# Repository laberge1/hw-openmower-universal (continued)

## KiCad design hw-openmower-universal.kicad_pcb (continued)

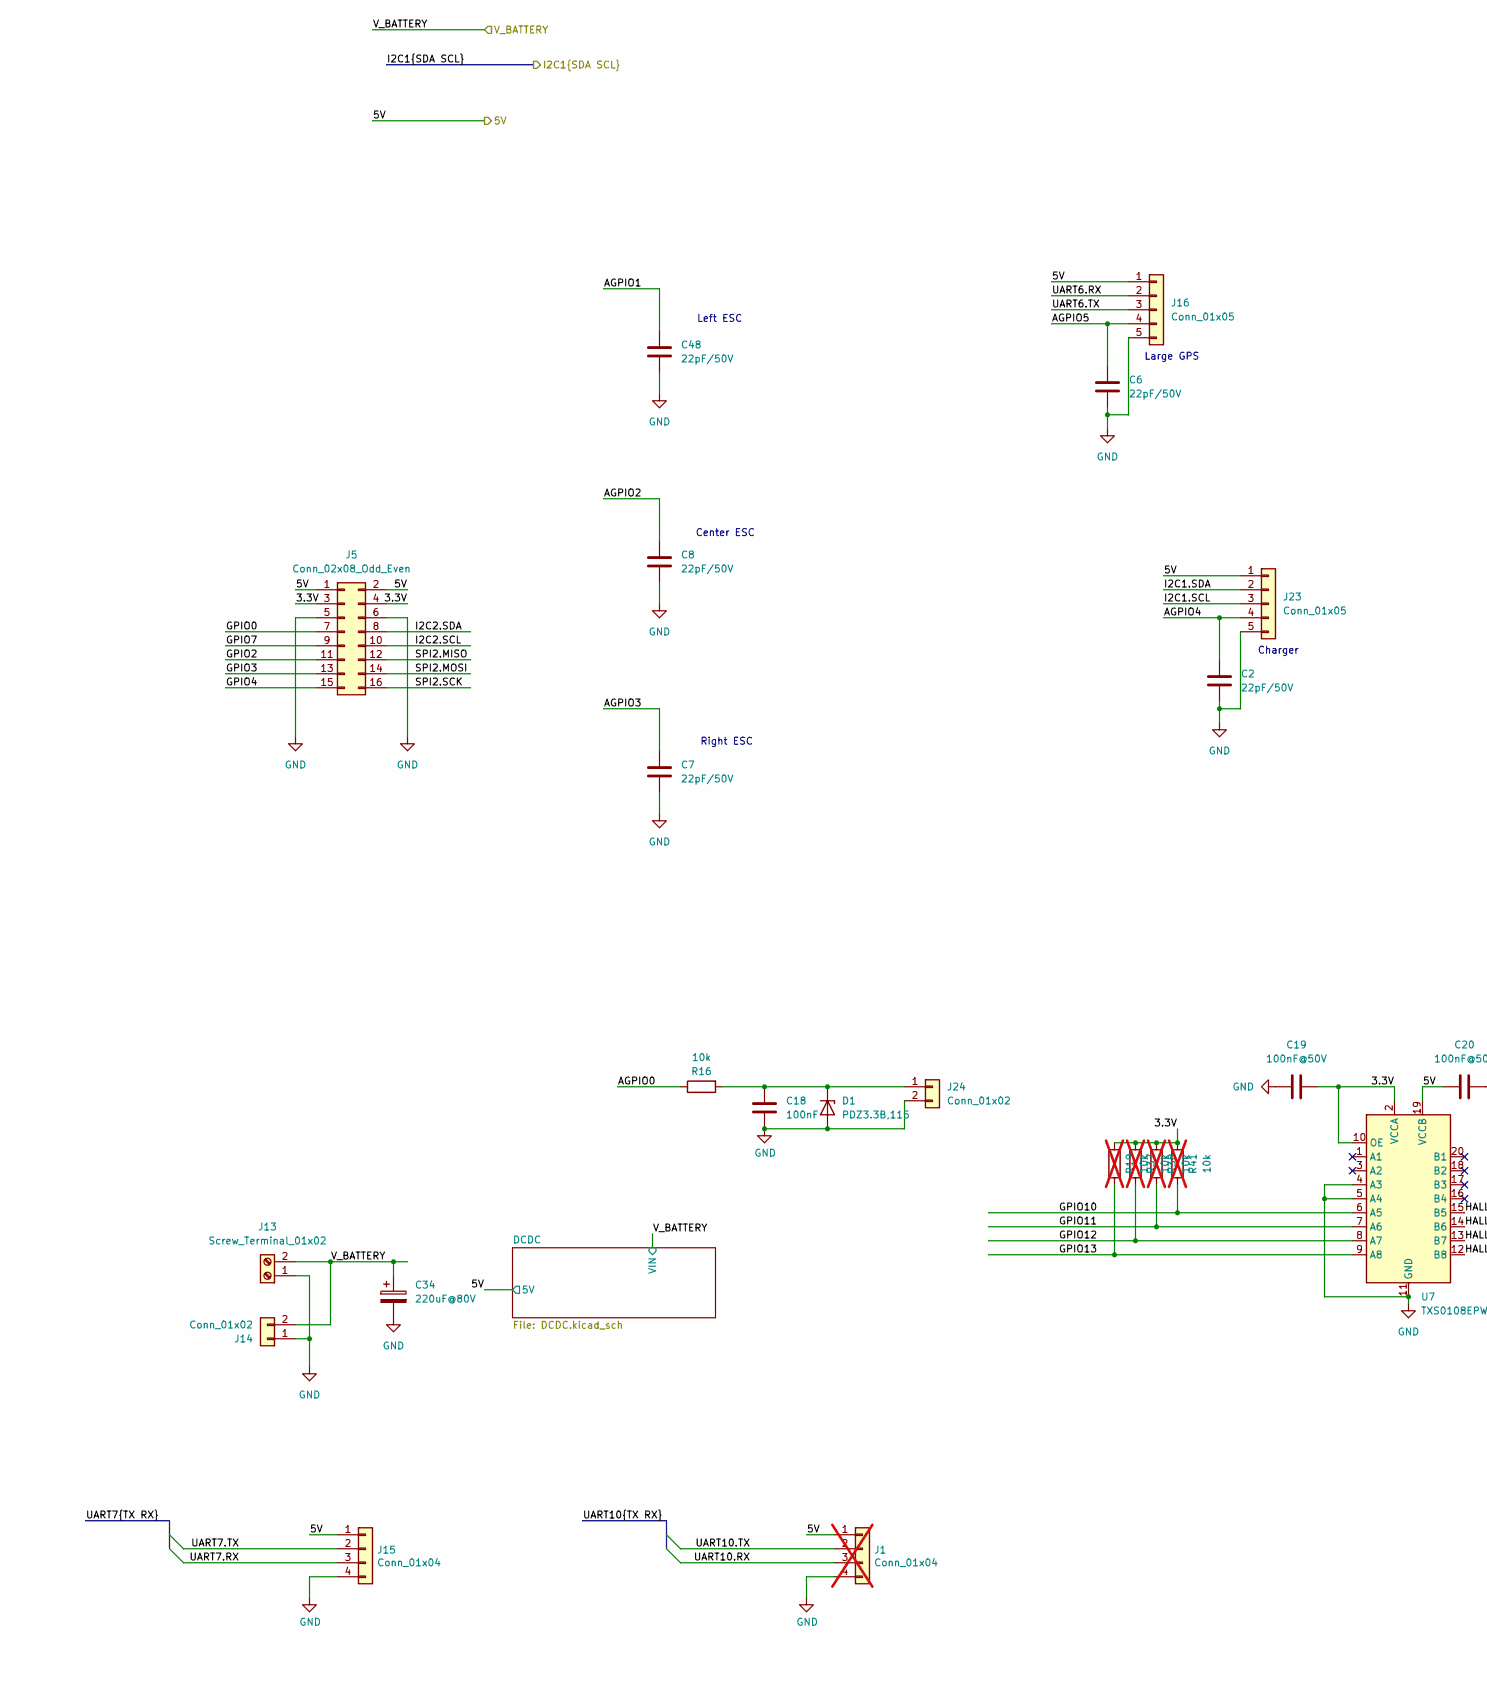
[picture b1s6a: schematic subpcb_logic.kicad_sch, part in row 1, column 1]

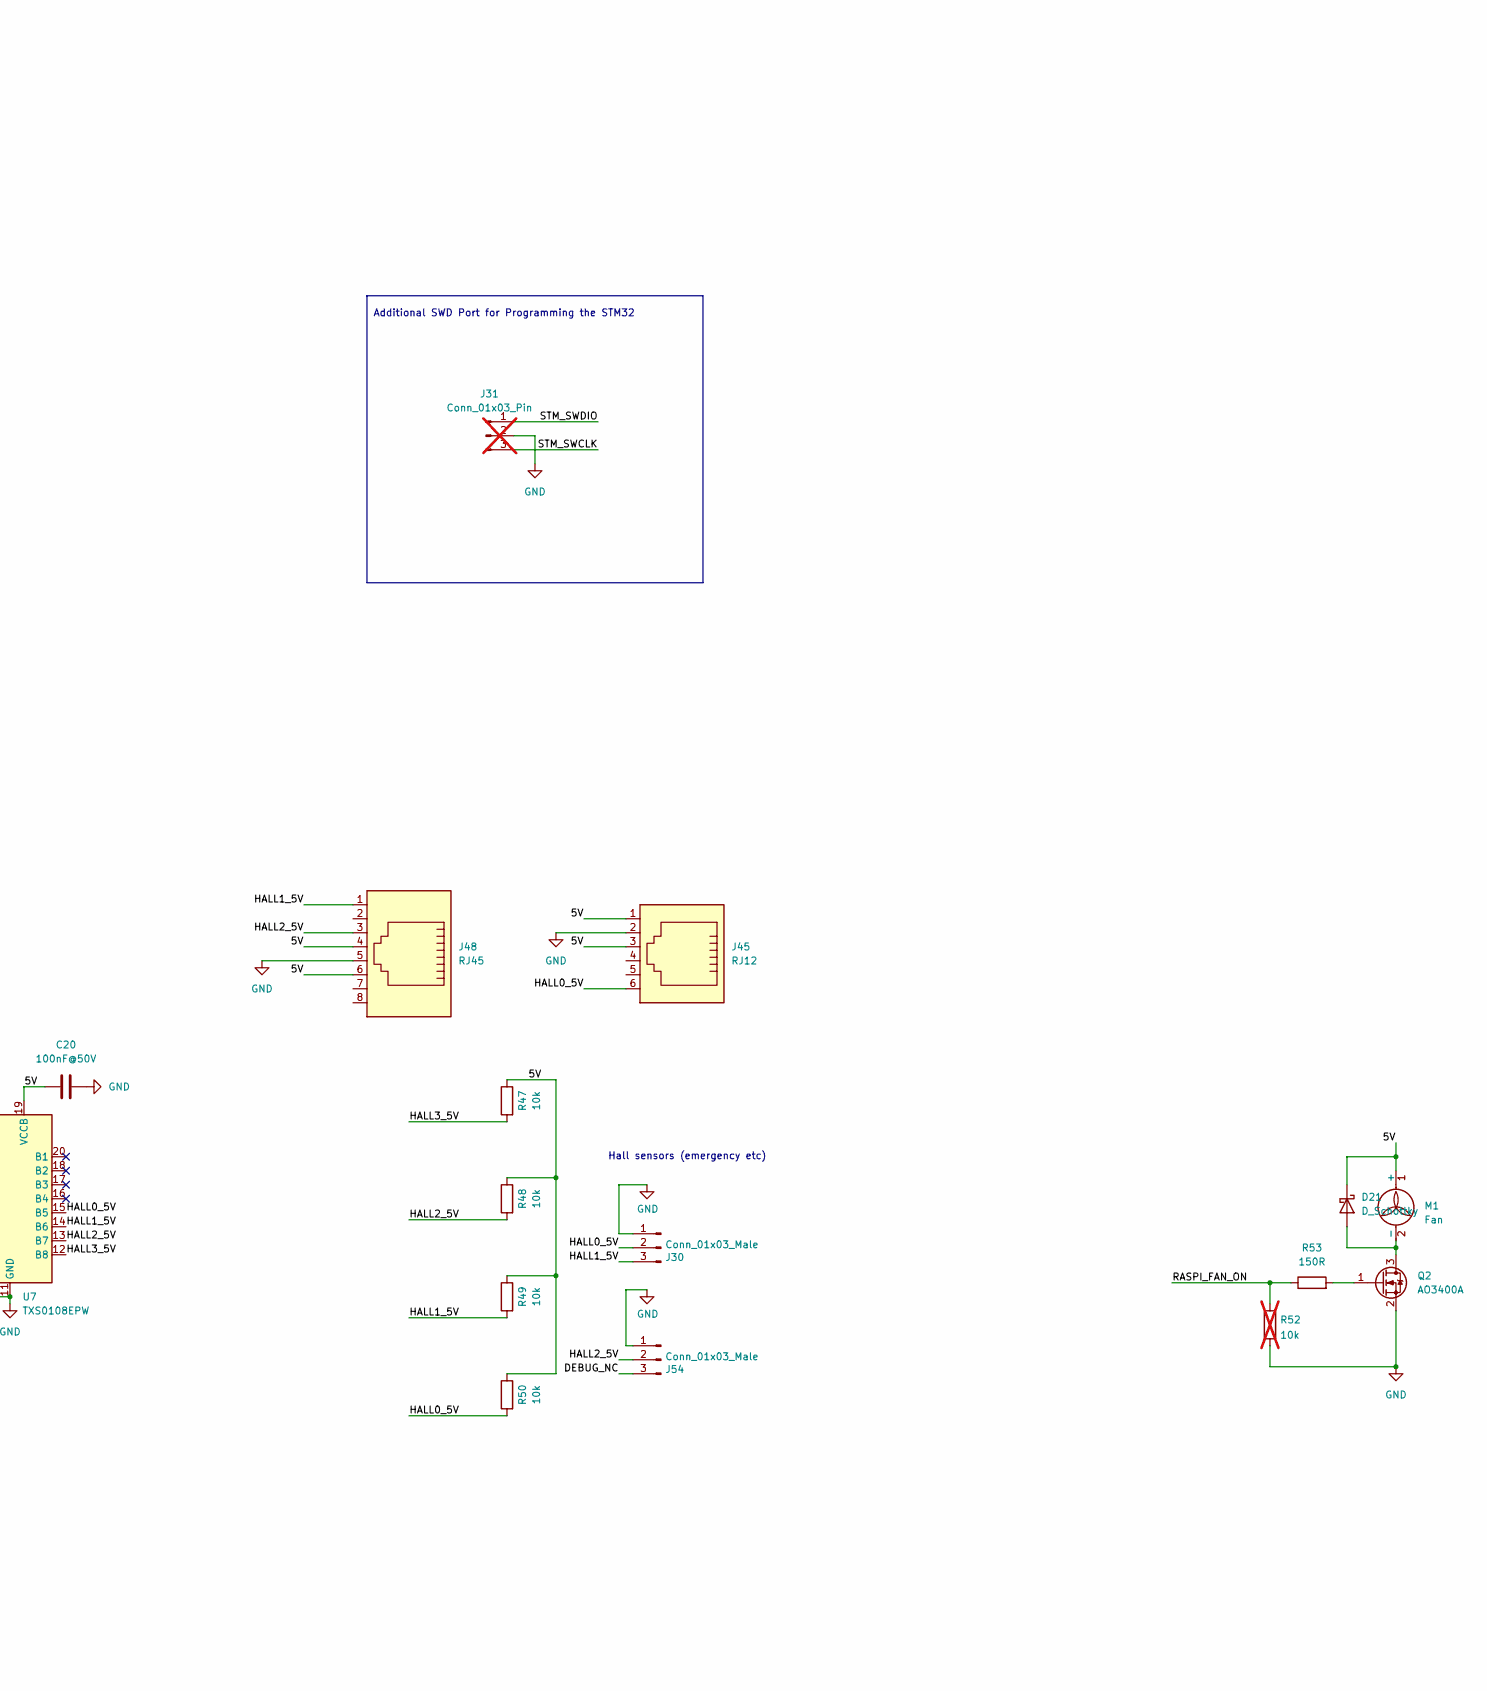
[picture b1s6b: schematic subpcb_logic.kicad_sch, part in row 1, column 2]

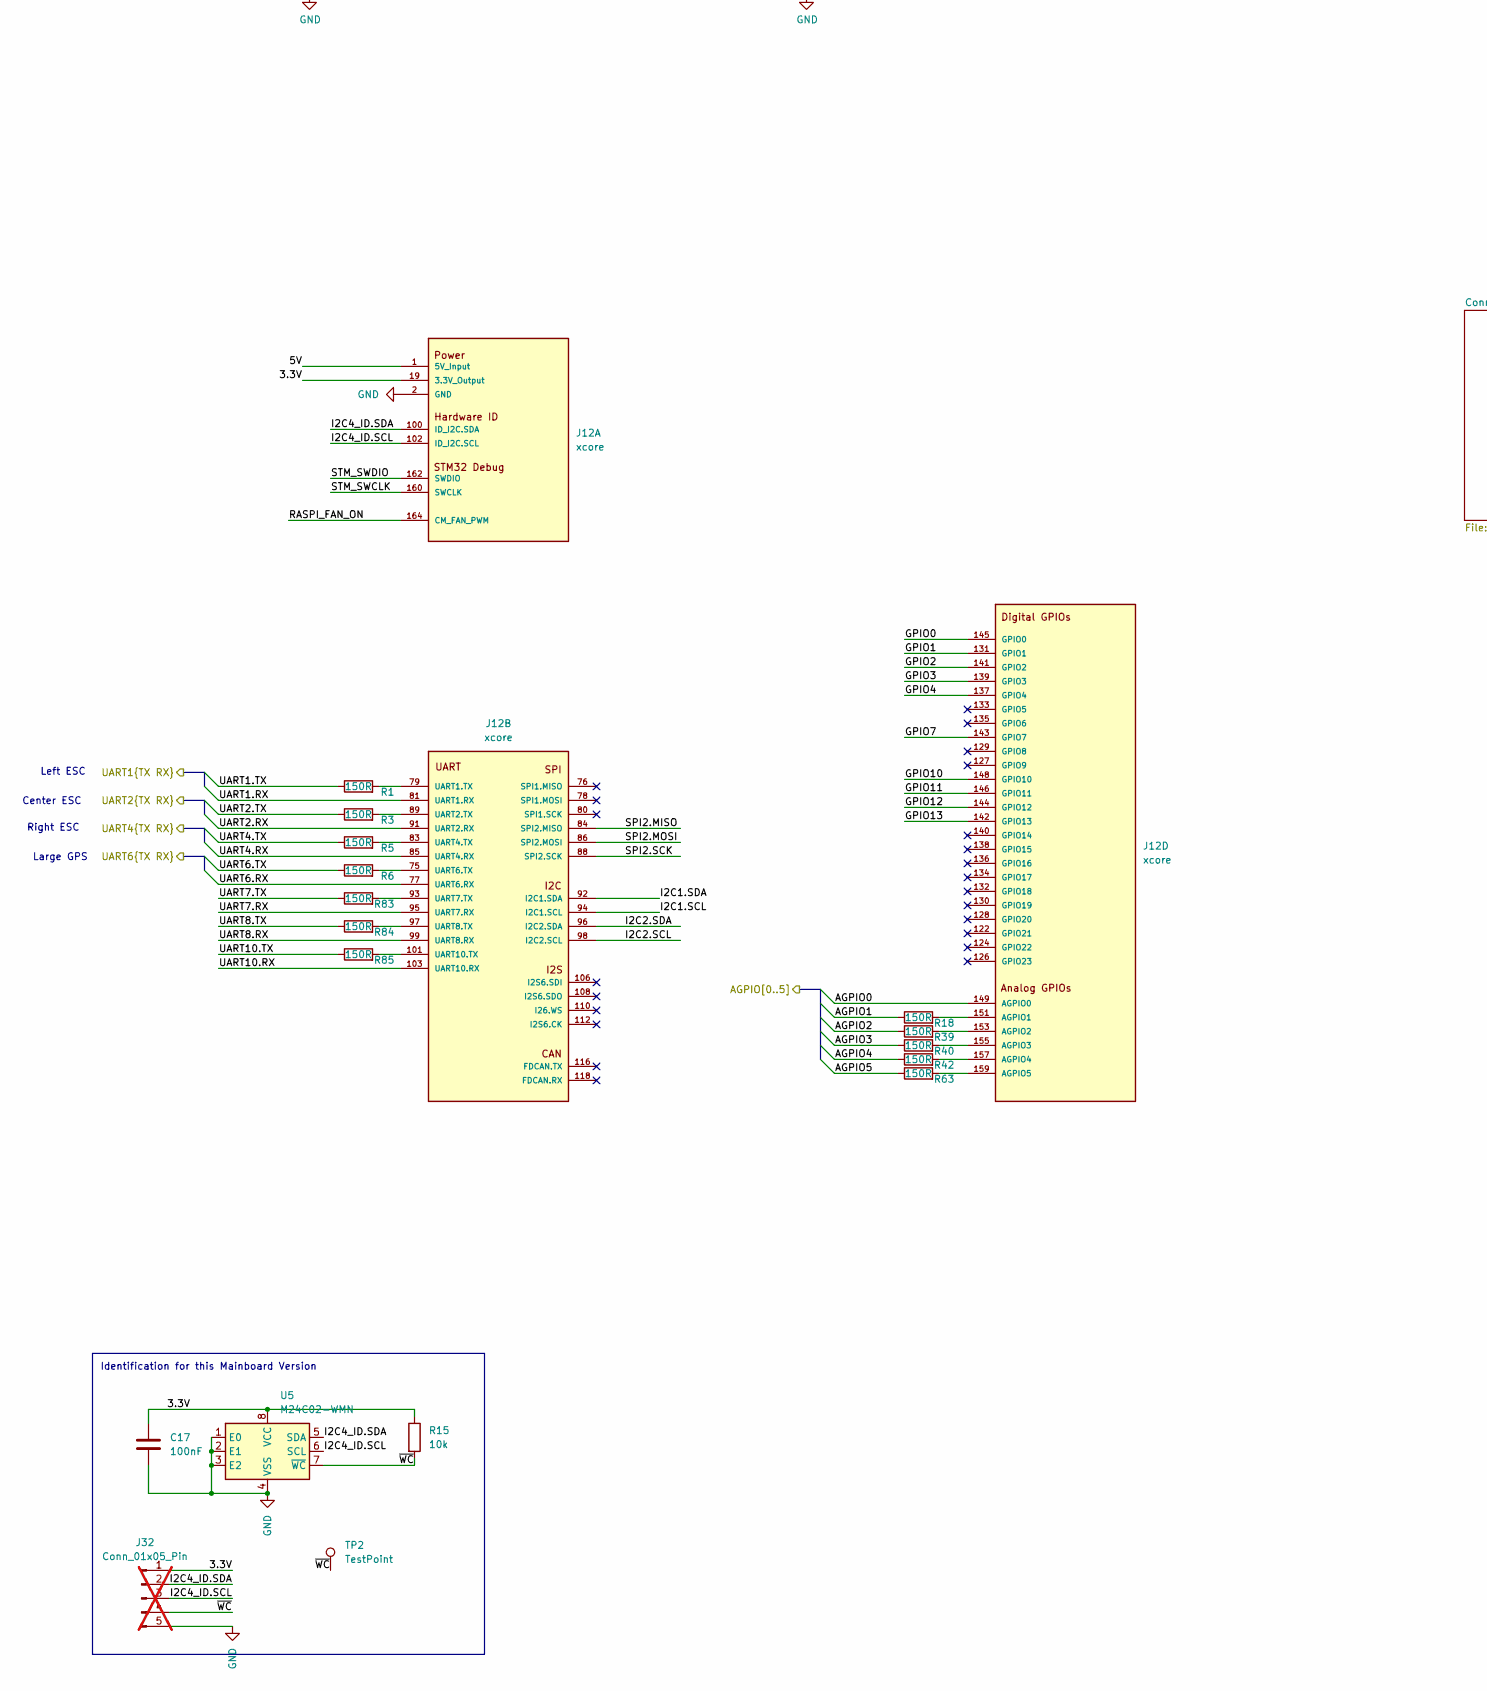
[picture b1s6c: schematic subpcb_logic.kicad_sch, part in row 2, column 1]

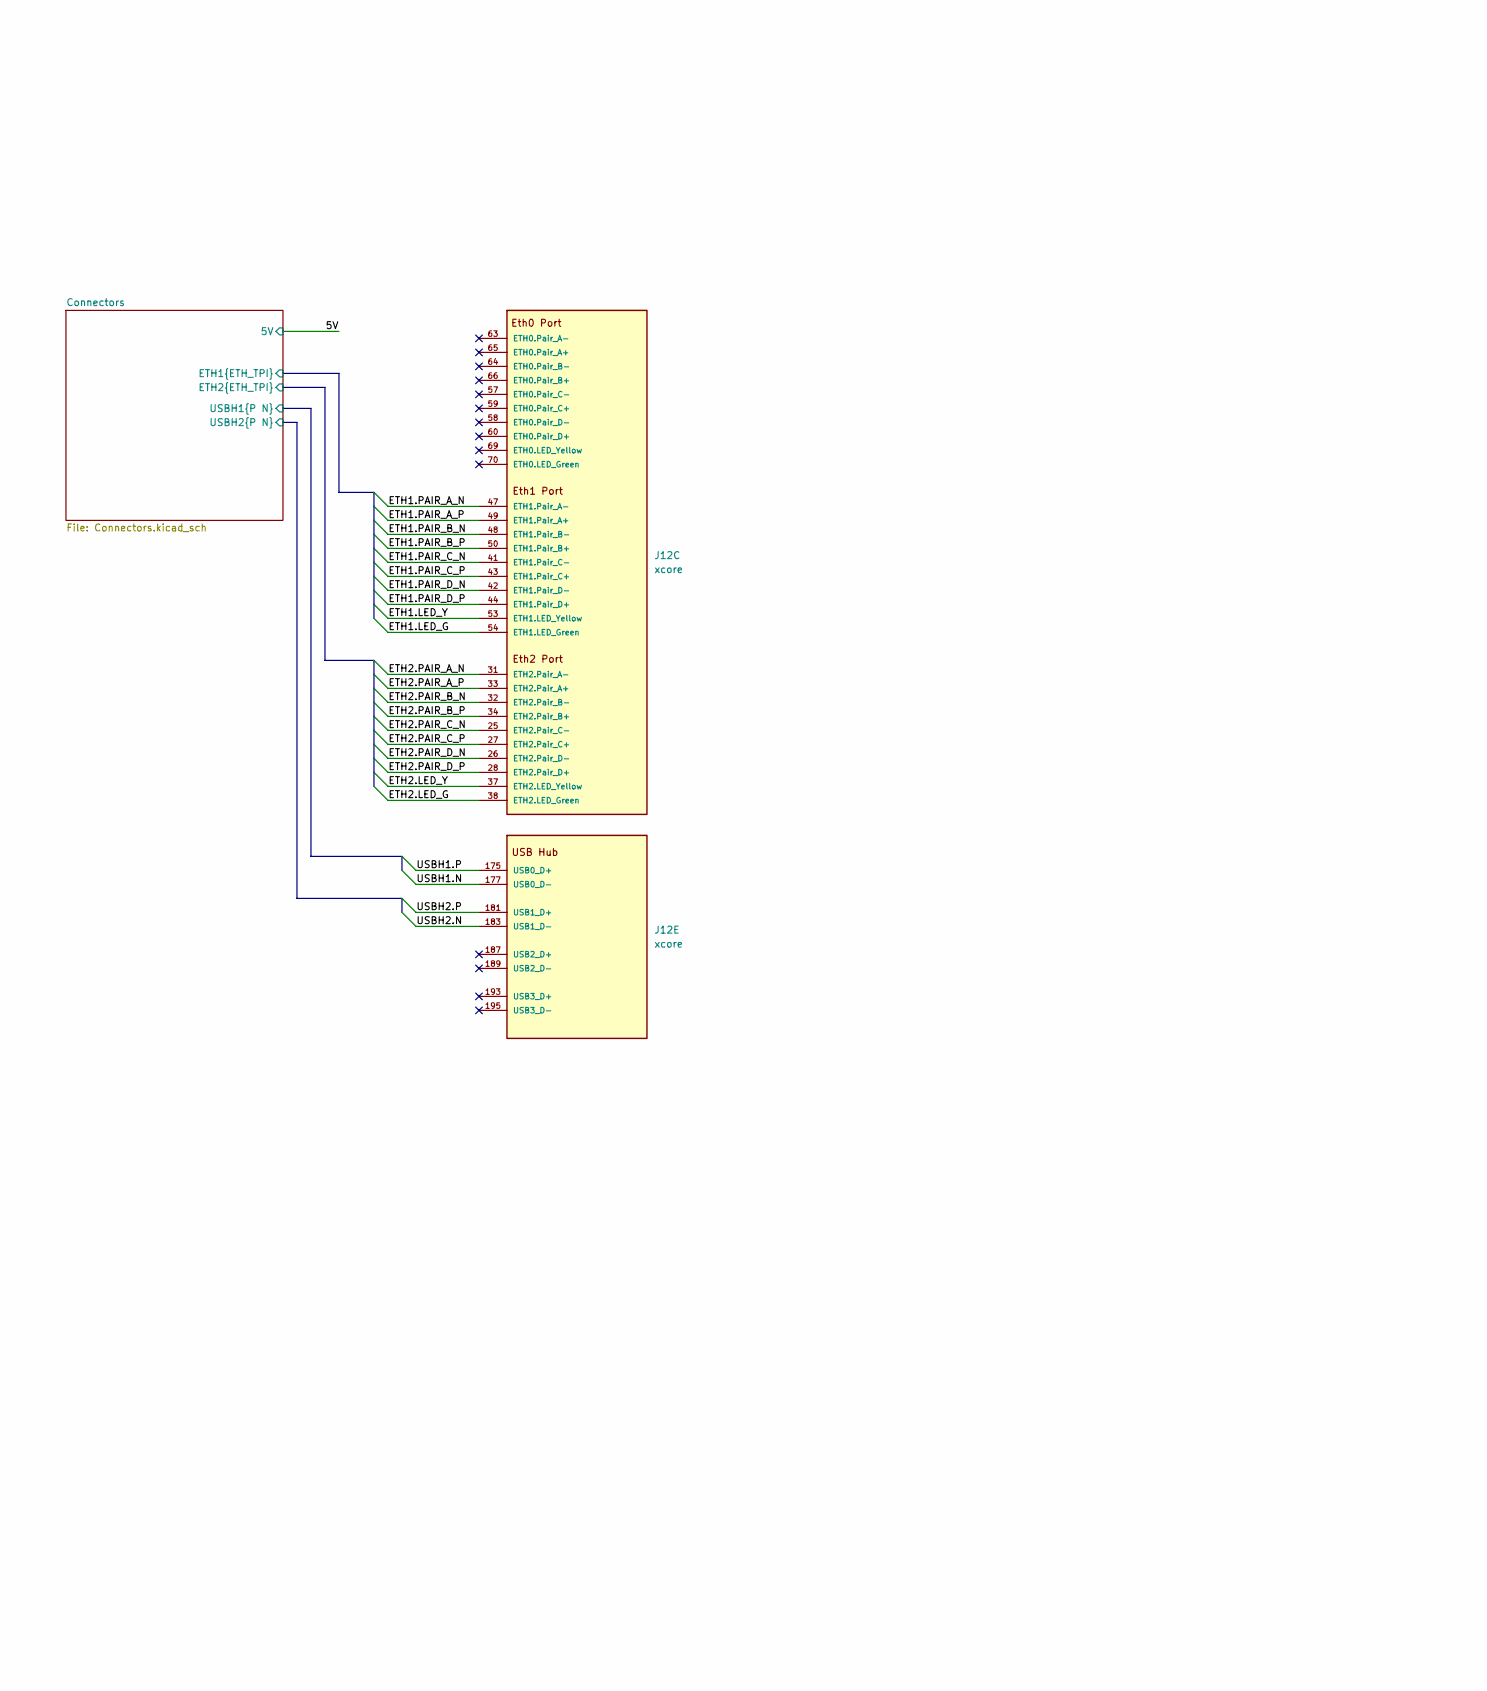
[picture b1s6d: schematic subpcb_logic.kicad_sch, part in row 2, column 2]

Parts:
C2, C6, C7, C8, C48: 22pF/50V; C_0603_1608Metric; JLC C1653
C17, C18: 100nF; C_0402_1005Metric; JLC C307331
C19, C20: 100nF@50V; C_0402_1005Metric; JLC C307331
C34: 220uF@80V; CP_Radial_D10.0mm_P5.00mm; JLC C106516
D1: PDZ3.3B,115; D_SOD-323; JLC C426855
D21: D_Schottky; D_SOD-123F; Part Number AS160-M; Digikey 3757-SS0520_R1_00001CT-ND
J1: Conn_01x04; JST_XH_B4B-XH-A_1x04_P2.50mm_Vertical; Part Number B4B-XH-A(LF)(SN); Digikey 455-2249-ND; not fitted
J5: Conn_02x08_Odd_Even; PinHeader_2x08_P2.54mm_Vertical; JLC C779499
J12: xcore; JLC C306045
J13: Screw_Terminal_01x02; TerminalBlock_Phoenix_MKDS-1,5-2-5.08_1x02_P5.08mm_Horizont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; JLC C557665
J14: Conn_01x02; AMASS_XT30U-M_1x02_P5.0mm_Vertical; JLC C99101
J15: Conn_01x04; JST_XH_B4B-XH-A_1x04_P2.50mm_Vertical; Part Number B4B-XH-A(LF)(SN); Digikey 455-2249-ND
J16, J23: Conn_01x05; JST_XH_B5B-XH-A_1x05_P2.50mm_Vertical; JLC C157991
J24: Conn_01x02; JST_XH_B2B-XH-A_1x02_P2.50mm_Vertical; Part Number B2B-XH-A-GU; Digikey 455-2946-ND
J30, J54: Conn_01x03_Male; PinHeader_1x03_P2.54mm_Vertical; Part Number B3B-XH-AM(LF)(SN); Digikey 455-2231-ND
J31: Conn_01x03_Pin; PinHeader_1x03_P2.54mm_Vertical; not fitted
J32: Conn_01x05_Pin; PinHeader_1x05_P2.54mm_Vertical; not fitted
J45: RJ12; CONN_85513-5002_MOL; Digikey PN WM3789CT-ND
J48: RJ45; RJ45_Molex_0855135013_Vertical; Digikey PN WM3553CT-ND
M1: Fan; PinHeader_1x02_P2.54mm_Vertical; Part Number DZ254R-11-02-63; JLC C2935908
Q2: AO3400A; SOT-23; Part Number AP2300; Digikey BSS138K-13DICT-ND
R1, R3, R5, R6, R18, R39, R40, R42, R63, R83, R84, R85: 150R; R_0603_1608Metric; JLC C22808
R15, R16, R47, R48, R49, R50: 10k; R_0402_1005Metric; JLC C25744
R19, R37, R38, R41: 10k; R_0402_1005Metric; JLC C25744; not fitted
R52: 10k; R_0805_2012Metric_Pad1.20x1.40mm_HandSolder; Part Number RMCF0805FG10K0; Digikey 738-RMCF0805FG10K0CT-ND; not fitted
R53: 150R; R_0805_2012Metric_Pad1.20x1.40mm_HandSolder; Part Number RC0805FR-07150RL; Digikey 311-150CRCT-ND
TP2: TestPoint; Pin_D1.4mm_L8.5mm_W2.8mm_FlatFork
U5: M24C02-WMN; SOIC-8_3.9x4.9mm_P1.27mm; JLC C7562
U7: TXS0108EPW; TSSOP-20_4.4x6.5mm_P0.65mm; JLC C17206

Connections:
/5V: C20.1, D21.1 (K), J1.1, J5.1, J5.2, J12.1 (5V_Input), J12.3 (5V_Input), J12.5 (5V_Input), J12.7 (5V_Input), J12.9 (5V_Input), J12.11 (5V_Input), J12.13 (5V_Input), J12.15 (5V_Input), J12.17 (5V_Input), J15.1, J16.1, J23.1, J45.1, J45.3, J48.4, J48.6, M1.1 (+), R47.1, R48.1, R49.1, R50.1, U7.19 (VCCB); also elsewhere on the board
/UART1.RX: J12.81 (UART1.RX); also elsewhere on the board
/UART1.TX: R1.1; also elsewhere on the board
/UART2.RX: J12.91 (UART2.RX); also elsewhere on the board
/UART2.TX: R3.1; also elsewhere on the board
/UART4.RX: J12.85 (UART4.RX); also elsewhere on the board
/UART4.TX: R5.1; also elsewhere on the board
/V_BATTERY: C34.1, J13.2, J14.2; also elsewhere on the board
/subpcb_logic/3.3V: C17.1, C19.1, J5.3, J5.4, J12.19 (3.3V_Output), J12.21 (3.3V_Output), J32.1, R15.1, R19.1, R37.1, R38.1, R41.1, U5.8 (VCC), U7.2 (VCCA), U7.10 (OE)
/subpcb_logic/AGPIO0: J12.149 (AGPIO0), R16.1
/subpcb_logic/AGPIO1: C48.1, R18.1; also elsewhere on the board
/subpcb_logic/AGPIO2: C8.1, R39.1; also elsewhere on the board
/subpcb_logic/AGPIO3: C7.1, R40.1; also elsewhere on the board
/subpcb_logic/AGPIO4: C2.1, J23.4, R42.1
/subpcb_logic/AGPIO5: C6.1, J16.4, R63.1
/subpcb_logic/Connectors/ETH1.LED_G: J12.54 (ETH1.LED_Green); also elsewhere on the board
/subpcb_logic/Connectors/ETH1.LED_Y: J12.53 (ETH1.LED_Yellow); also elsewhere on the board
/subpcb_logic/Connectors/ETH1.PAIR_A_N: J12.47 (ETH1.Pair_A-); also elsewhere on the board
/subpcb_logic/Connectors/ETH1.PAIR_A_P: J12.49 (ETH1.Pair_A+); also elsewhere on the board
/subpcb_logic/Connectors/ETH1.PAIR_B_N: J12.48 (ETH1.Pair_B-); also elsewhere on the board
/subpcb_logic/Connectors/ETH1.PAIR_B_P: J12.50 (ETH1.Pair_B+); also elsewhere on the board
/subpcb_logic/Connectors/ETH1.PAIR_C_N: J12.41 (ETH1.Pair_C-); also elsewhere on the board
/subpcb_logic/Connectors/ETH1.PAIR_C_P: J12.43 (ETH1.Pair_C+); also elsewhere on the board
/subpcb_logic/Connectors/ETH1.PAIR_D_N: J12.42 (ETH1.Pair_D-); also elsewhere on the board
/subpcb_logic/Connectors/ETH1.PAIR_D_P: J12.44 (ETH1.Pair_D+); also elsewhere on the board
/subpcb_logic/Connectors/ETH2.LED_G: J12.38 (ETH2.LED_Green); also elsewhere on the board
/subpcb_logic/Connectors/ETH2.LED_Y: J12.37 (ETH2.LED_Yellow); also elsewhere on the board
/subpcb_logic/Connectors/ETH2.PAIR_A_N: J12.31 (ETH2.Pair_A-); also elsewhere on the board
/subpcb_logic/Connectors/ETH2.PAIR_A_P: J12.33 (ETH2.Pair_A+); also elsewhere on the board
/subpcb_logic/Connectors/ETH2.PAIR_B_N: J12.32 (ETH2.Pair_B-); also elsewhere on the board
/subpcb_logic/Connectors/ETH2.PAIR_B_P: J12.34 (ETH2.Pair_B+); also elsewhere on the board
/subpcb_logic/Connectors/ETH2.PAIR_C_N: J12.25 (ETH2.Pair_C-); also elsewhere on the board
/subpcb_logic/Connectors/ETH2.PAIR_C_P: J12.27 (ETH2.Pair_C+); also elsewhere on the board
/subpcb_logic/Connectors/ETH2.PAIR_D_N: J12.26 (ETH2.Pair_D-); also elsewhere on the board
/subpcb_logic/Connectors/ETH2.PAIR_D_P: J12.28 (ETH2.Pair_D+); also elsewhere on the board
/subpcb_logic/Connectors/USBH1.N: J12.177 (USB0_D-); also elsewhere on the board
/subpcb_logic/Connectors/USBH1.P: J12.175 (USB0_D+); also elsewhere on the board
/subpcb_logic/Connectors/USBH2.N: J12.183 (USB1_D-); also elsewhere on the board
/subpcb_logic/Connectors/USBH2.P: J12.181 (USB1_D+); also elsewhere on the board
/subpcb_logic/DEBUG_NC: J54.3
/subpcb_logic/GPIO0: J5.7, J12.145 (GPIO0)
/subpcb_logic/GPIO1: J12.131 (GPIO1)
/subpcb_logic/GPIO2: J5.11, J12.141 (GPIO2)
/subpcb_logic/GPIO3: J5.13, J12.139 (GPIO3)
/subpcb_logic/GPIO4: J5.15, J12.137 (GPIO4)
/subpcb_logic/GPIO7: J5.9, J12.143 (GPIO7)
/subpcb_logic/GPIO10: J12.148 (GPIO10), R41.2, U7.6 (A5)
/subpcb_logic/GPIO11: J12.146 (GPIO11), R38.2, U7.7 (A6)
/subpcb_logic/GPIO12: J12.144 (GPIO12), R37.2, U7.8 (A7)
/subpcb_logic/GPIO13: J12.142 (GPIO13), R19.2, U7.9 (A8)
/subpcb_logic/HALL0_5V: J30.2, J45.6, R50.2, U7.15 (B5)
/subpcb_logic/HALL1_5V: J30.3, J48.1, R49.2, U7.14 (B6)
/subpcb_logic/HALL2_5V: J48.3, J54.2, R48.2, U7.13 (B7)
/subpcb_logic/HALL3_5V: R47.2, U7.12 (B8)
/subpcb_logic/I2C1.SCL: J12.94 (I2C1.SCL), J23.3
/subpcb_logic/I2C1.SDA: J12.92 (I2C1.SDA), J23.2
/subpcb_logic/I2C2.SCL: J5.10, J12.98 (I2C2.SCL)
/subpcb_logic/I2C2.SDA: J5.8, J12.96 (I2C2.SDA)
/subpcb_logic/I2C4_ID.SCL: J12.102 (ID_I2C.SCL), J32.3, U5.6 (SCL)
/subpcb_logic/I2C4_ID.SDA: J12.100 (ID_I2C.SDA), J32.2, U5.5 (SDA)
/subpcb_logic/RASPI_FAN_ON: J12.164 (CM_FAN_PWM), R52.2, R53.1
/subpcb_logic/SPI2.MISO: J5.12, J12.84 (SPI2.MISO)
/subpcb_logic/SPI2.MOSI: J5.14, J12.86 (SPI2.MOSI)
/subpcb_logic/SPI2.SCK: J5.16, J12.88 (SPI2.SCK)
/subpcb_logic/STM_SWCLK: J12.160 (SWCLK), J31.3
/subpcb_logic/STM_SWDIO: J12.162 (SWDIO), J31.1
/subpcb_logic/UART6.RX: J12.77 (UART6.RX), J16.2
/subpcb_logic/UART6.TX: J16.3, R6.1
/subpcb_logic/UART7.RX: J12.95 (UART7.RX), J15.3
/subpcb_logic/UART7.TX: J15.2, R83.1
/subpcb_logic/UART8.RX: J12.99 (UART8.RX)
/subpcb_logic/UART8.TX: R84.1
/subpcb_logic/UART10.RX: J1.3, J12.103 (UART10.RX)
/subpcb_logic/UART10.TX: J1.2, R85.1
/subpcb_logic/~WC: J32.4, R15.2, TP2.1, U5.7 (~WC)
GND: C2.2, C6.2, C7.2, C8.2, C17.2, C18.2, C19.2, C20.2, C34.2, C48.2, D1.2 (A), J1.4, J5.5, J5.6, J12.2 (GND), J12.4 (GND), J12.6 (GND), J12.8 (GND), J12.10 (GND), J12.12 (GND), J12.14 (GND), J12.16 (GND), J12.18 (GND), J12.23 (GND), J12.24 (GND), J12.29 (GND), J12.30 (GND), J12.35 (GND), J12.36 (GND), J12.39 (GND), J12.40 (GND), J12.45 (GND), J12.46 (GND), J12.51 (GND), J12.52 (GND), J12.55 (GND), J12.56 (GND), J12.61 (GND), J12.62 (GND), J12.67 (GND), J12.68 (GND), J12.71 (GND), J12.72 (GND), J12.73 (GND), J12.74 (GND), J12.82 (GND), J12.87 (GND), J12.90 (GND), J12.104 (GND), J12.114 (GND), J12.120 (GND), J12.147 (GND), J12.168 (GND), J12.173 (GND), J12.174 (GND), J12.179 (GND), J12.180 (GND), J12.185 (GND), J12.186 (GND), J12.191 (GND), J12.192 (GND), J12.197 (GND), J12.198 (GND), J12.203 (GND), J12.204 (GND), J12.SH1 (GND), J12.SH2 (GND), J13.1, J14.1, J15.4, J16.5, J23.5, J24.2, J30.1, J31.2, J32.5, J45.2, J48.5, J54.1, Q2.2 (S), R52.1, U5.1 (E0), U5.2 (E1), U5.3 (E2), U5.4 (VSS), U7.4 (A3), U7.5 (A4), U7.11 (GND); also elsewhere on the board
unnamed: C18.1, D1.1 (K), J24.1, R16.2
unnamed: D21.2 (A), M1.2 (-), Q2.3 (D)
unnamed: J12.79 (UART1.TX), R1.2
unnamed: J12.89 (UART2.TX), R3.2
unnamed: J12.83 (UART4.TX), R5.2
unnamed: J12.75 (UART6.TX), R6.2
unnamed: J12.93 (UART7.TX), R83.2
unnamed: J12.97 (UART8.TX), R84.2
unnamed: J12.101 (UART10.TX), R85.2
unnamed: J12.151 (AGPIO1), R18.2
unnamed: J12.153 (AGPIO2), R39.2
unnamed: J12.155 (AGPIO3), R40.2
unnamed: J12.157 (AGPIO4), R42.2
unnamed: J12.159 (AGPIO5), R63.2
unnamed: Q2.1 (G), R53.2

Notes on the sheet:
Hall sensors (emergency etc)
Right ESC
Charger
Center ESC
Identification for this Mainboard Version
Large GPS
Additional SWD Port for Programming the STM32
Left ESC

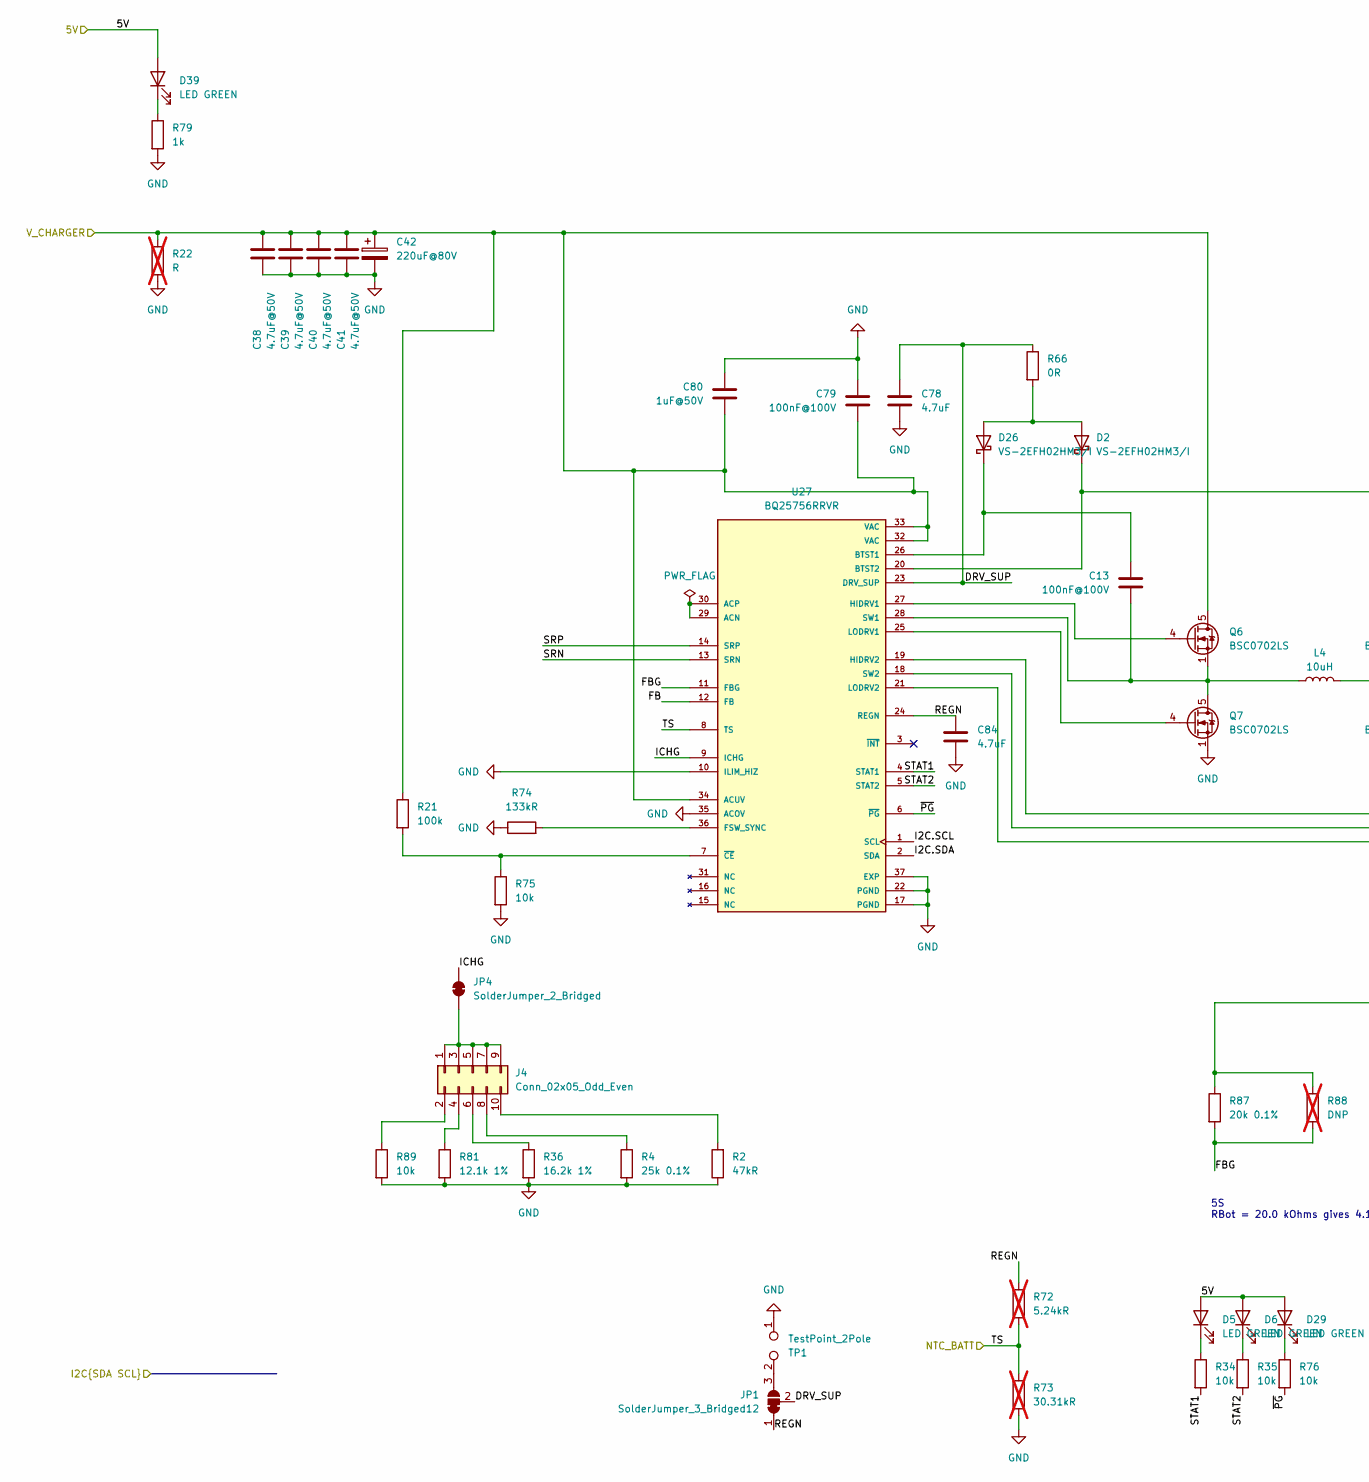
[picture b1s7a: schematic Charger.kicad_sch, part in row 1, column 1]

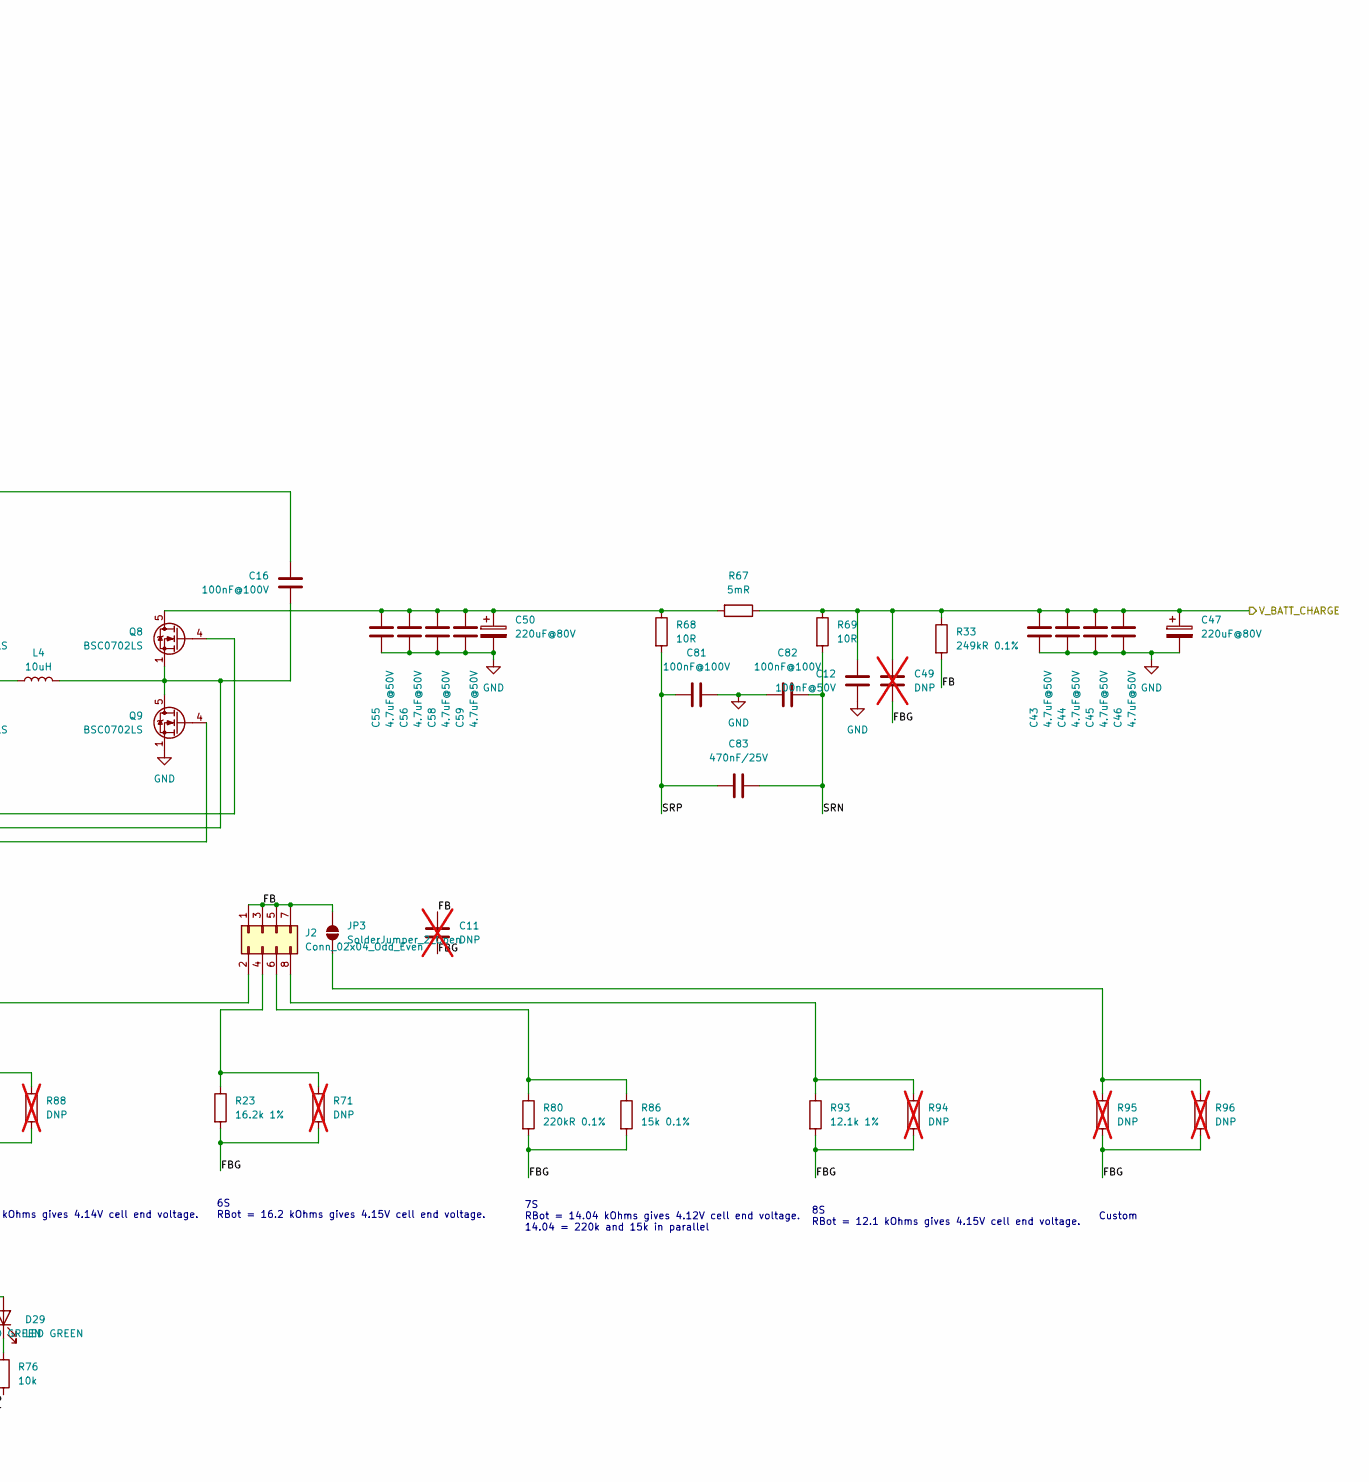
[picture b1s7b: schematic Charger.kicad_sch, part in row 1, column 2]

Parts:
C11, C49: DNP; C_0603_1608Metric; not fitted
C12: 100nF@50V; C_0603_1608Metric; JLC C14663
C13, C16, C79, C81, C82: 100nF@100V; C_0805_2012Metric; JLC C28233
C38, C39, C40, C41, C43, C44, C45, C46, C55, C56, C58, C59: 4.7uF@50V; C_1206_3216Metric; JLC C29823
C42, C47, C50: 220uF@80V; CP_Radial_D10.0mm_P5.00mm; JLC C106516
C78, C84: 4.7uF; C_0805_2012Metric; JLC C1779
C80: 1uF@50V; C_0805_2012Metric; JLC C354368
C83: 470nF/25V; C_0603_1608Metric; JLC C1623
D2, D26: VS-2EFH02HM3/I; D_SMF; JLC C241868
D5, D6, D29, D39: LED GREEN; LED_0805_2012Metric; JLC C2297
J2: Conn_02x04_Odd_Even; PinHeader_2x04_P2.54mm_Vertical; JLC C5383105
J4: Conn_02x05_Odd_Even; PinHeader_2x05_P2.54mm_Vertical; JLC C706895
JP1: SolderJumper_3_Bridged12; SolderJumper-3_P1.3mm_Bridged12_Pad1.0x1.5mm
JP3: SolderJumper_2_Open; SolderJumper-2_P1.3mm_Open_Pad1.0x1.5mm
JP4: SolderJumper_2_Bridged; SolderJumper-2_P1.3mm_Bridged_Pad1.0x1.5mm
L4: 10uH; L_Sunlord_MWSA1004S; JLC C408487
Q6, Q7, Q8, Q9: BSC0702LS; TDSON-8-1; JLC C501503
R2: 47kR; R_0603_1608Metric; JLC C25819
R4: 25k 0.1%; R_0603_1608Metric; JLC C2828637
R21: 100k; R_0402_1005Metric; JLC C25741
R22: R; R_1206_3216Metric; not fitted
R23, R36: 16.2k 1%; R_0603_1608Metric; JLC C22885
R33: 249kR 0.1%; R_0603_1608Metric; JLC C705752
R34, R35, R75, R76: 10k; R_0402_1005Metric; JLC C25744
R66: 0R; R_0805_2012Metric; JLC C17477
R67: 5mR; R_2512_6332Metric; JLC C309526
R68, R69: 10R; R_0603_1608Metric; JLC C22859
R71, R88, R94, R95, R96: DNP; R_0603_1608Metric; not fitted
R72: 5.24kR; R_0603_1608Metric; not fitted
R73: 30.31kR; R_0603_1608Metric; not fitted
R74: 133kR; R_0603_1608Metric; JLC C227577
R79: 1k; R_0805_2012Metric; JLC C17513
R80: 220kR 0.1%; R_0603_1608Metric; JLC C861231
R81, R93: 12.1k 1%; R_0603_1608Metric; JLC C22864
R86: 15k 0.1%; R_0603_1608Metric; JLC C2692707
R87: 20k 0.1%; R_0603_1608Metric; JLC C4184
R89: 10k; R_0603_1608Metric; JLC C25804
TP1: TestPoint_2Pole; PinHeader_1x02_P2.54mm_Vertical
U27: BQ25756RRVR; PARTREV August 2023; JLC C19272232

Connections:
/subpcb_charger/5V: D5.2 (A), D6.2 (A), D29.2 (A), D39.2 (A); also elsewhere on the board
/subpcb_charger/Charger/DRV_SUP: C78.1, JP1.2 (C), R66.1, U27.23 (DRV_SUP)
/subpcb_charger/Charger/FB: C11.1, J2.1, J2.3, J2.5, J2.7, JP3.2 (B), R33.2, U27.12 (FB)
/subpcb_charger/Charger/FBG: C11.2, C49.2, R23.2, R71.2, R80.2, R86.2, R87.2, R88.2, R93.2, R94.2, R95.2, R96.2, U27.11 (FBG)
/subpcb_charger/Charger/ICHG: JP4.2 (B), U27.9 (ICHG)
/subpcb_charger/Charger/SRN: C82.1, C83.2, R69.2, U27.13 (SRN)
/subpcb_charger/Charger/SRP: C81.2, C83.1, R68.2, U27.14 (SRP)
/subpcb_charger/Charger/STAT1: R34.2, U27.4 (STAT1)
/subpcb_charger/Charger/STAT2: R35.2, U27.5 (STAT2)
/subpcb_charger/Charger/V_BATT_CHARGE: C12.2, C43.1, C44.1, C45.1, C46.1, C47.1, C49.1, R33.1, R67.1, R69.1; also elsewhere on the board
/subpcb_charger/Charger/~PG: R76.2, U27.6 (~PG)
/subpcb_charger/I2C.SCL: U27.1 (SCL); also elsewhere on the board
/subpcb_charger/I2C.SDA: U27.2 (SDA); also elsewhere on the board
/subpcb_charger/NTC_BATT: R72.2, R73.1, U27.8 (TS); also elsewhere on the board
/subpcb_charger/V_CHARGE: C38.1, C39.1, C40.1, C41.1, C42.1, C79.1, C80.1, Q6.5 (D), R21.1, R22.1, U27.32 (VAC), U27.33 (VAC), U27.34 (ACUV); also elsewhere on the board
GND: C12.1, C38.2, C39.2, C40.2, C41.2, C42.2, C43.2, C44.2, C45.2, C46.2, C47.2, C50.2, C55.2, C56.2, C58.2, C59.2, C78.2, C79.2, C80.2, C81.1, C82.2, C84.2, Q7.1 (S), Q7.2 (S), Q7.3 (S), Q9.1 (S), Q9.2 (S), Q9.3 (S), R2.1, R4.2, R22.2, R36.2, R73.2, R74.1, R75.2, R79.2, R81.2, R89.2, TP1.1, U27.10 (ILIM_HIZ), U27.17 (PGND), U27.22 (PGND), U27.35 (ACOV), U27.37 (EXP); also elsewhere on the board
unnamed: D2.2 (A), D26.2 (A), R66.2
unnamed: C16.2, D2.1 (K), U27.20 (BTST2)
unnamed: D5.1 (K), R34.1
unnamed: D6.1 (K), R35.1
unnamed: C13.2, D26.1 (K), U27.26 (BTST1)
unnamed: D29.1 (K), R76.1
unnamed: D39.1 (K), R79.1
unnamed: J2.2, R87.1, R88.1
unnamed: J2.4, R23.1, R71.1
unnamed: J2.6, R80.1, R86.1
unnamed: J2.8, R93.1, R94.1
unnamed: J4.1, J4.3, J4.5, J4.7, J4.9, JP4.1 (A)
unnamed: J4.2, R89.1
unnamed: J4.4, R81.1
unnamed: J4.6, R36.1
unnamed: J4.8, R4.1
unnamed: J4.10, R2.2
unnamed: JP1.3 (B), TP1.2
unnamed: JP3.1 (A), R95.1, R96.1
unnamed: Q6.4 (G), U27.27 (HIDRV1)
unnamed: C13.1, L4.1, Q6.1 (S), Q6.2 (S), Q6.3 (S), Q7.5 (D), U27.28 (SW1)
unnamed: Q7.4 (G), U27.25 (LODRV1)
unnamed: C50.1, C55.1, C56.1, C58.1, C59.1, Q8.5 (D), R67.2, R68.1
unnamed: Q8.4 (G), U27.19 (HIDRV2)
unnamed: C16.1, L4.2, Q8.1 (S), Q8.2 (S), Q8.3 (S), Q9.5 (D), U27.18 (SW2)
unnamed: Q9.4 (G), U27.21 (LODRV2)
unnamed: U27.29 (ACN), U27.30 (ACP)
unnamed: R74.2, U27.36 (FSW_SYNC)
unnamed: R21.2, R75.1, U27.7 (~CE)

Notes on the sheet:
6S RBot = 16.2 kOhms gives 4.15V cell end voltage.
Custom
7S RBot = 14.04 kOhms gives 4.12V cell end voltage. 14.04 = 220k and 15k in parallel
5S RBot = 20.0 kOhms gives 4.14V cell end voltage.
8S RBot = 12.1 kOhms gives 4.15V cell end voltage.
